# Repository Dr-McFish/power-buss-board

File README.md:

# power-buss-board
power distribution PCB for a cosmo format sythesiser

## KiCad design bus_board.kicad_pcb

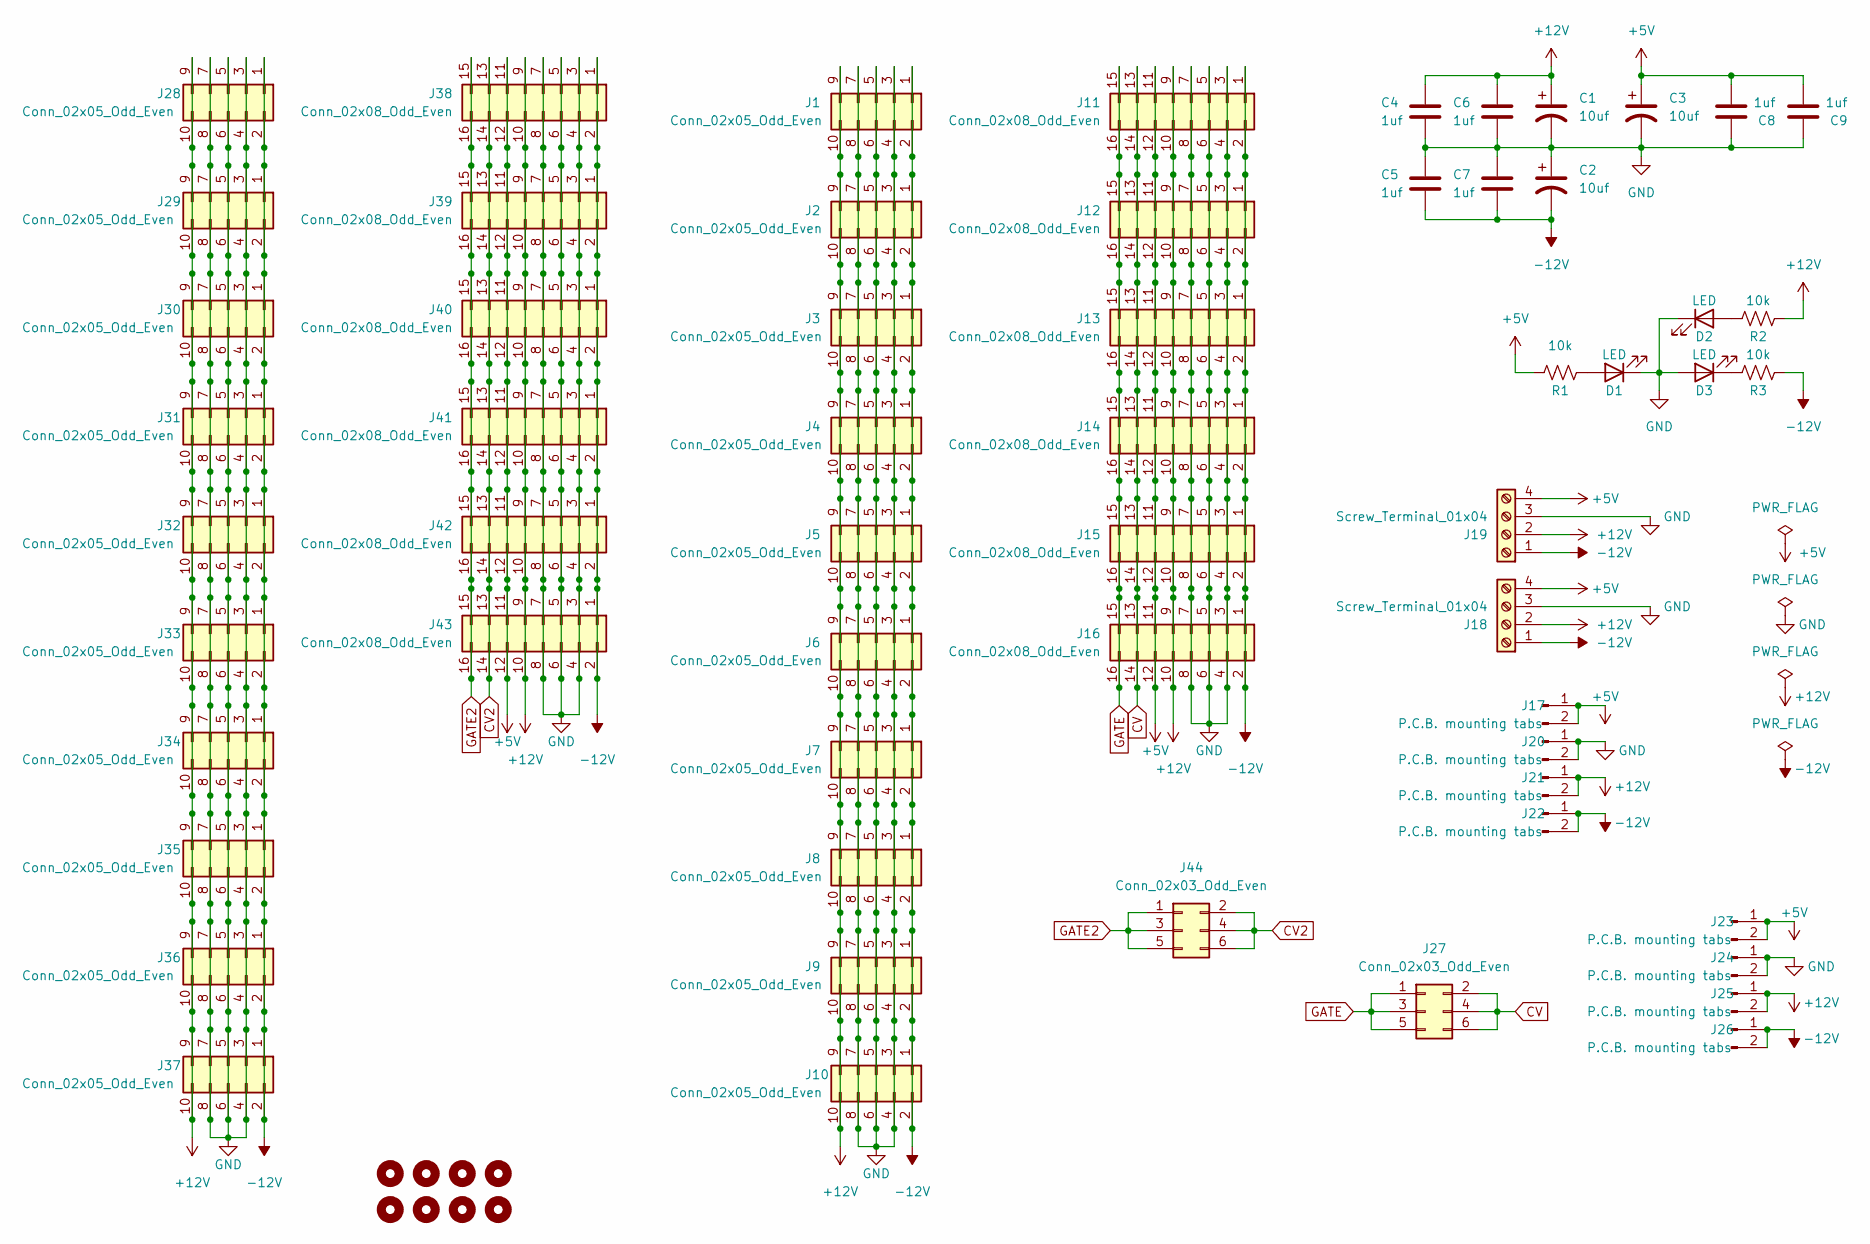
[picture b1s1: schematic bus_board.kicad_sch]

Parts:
C1, C2, C3: 10uf; CP_Radial_D5.0mm_P2.50mm
C4, C5, C6, C7, C8, C9: 1uf; C_Disc_D5.0mm_W2.5mm_P5.00mm
D1, D2, D3: LED; LED_D5.0mm_Clear
H1, H2, H3, H4, H5, H6, H7, H8: MountingHole; MountingHole_3.2mm_M3
J1, J2, J3, J4, J5, J6, J7, J8, J9, J10, J28, J29, J30, J31, J32, J33, J34, J35, J36, J37: Conn_02x05_Odd_Even; IDC-Header_2x05_P2.54mm_Vertical
J11, J12, J13, J14, J15, J16, J38, J39, J40, J41, J42, J43: Conn_02x08_Odd_Even; IDC-Header_2x08_P2.54mm_Vertical
J17, J20, J21, J22, J23, J24, J25, J26: P.C.B. mounting tabs; 3867B.68 P.C.B. mounting tab
J18, J19: Screw_Terminal_01x04; TerminalBlock_bornier-4_P5.08mm
J27, J44: Conn_02x03_Odd_Even; PinHeader_2x03_P2.54mm_Vertical
R1: 10k; R_Axial_DIN0207_L6.3mm_D2.5mm_P10.16mm_Horizontal
R2: 10k; R_Axial_DIN0207_L6.3mm_D2.5mm_P7.62mm_Horizontal
R3: 10k; R_Axial_DIN0207_L6.3mm_D2.5mm_P15.24mm_Horizontal

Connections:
+5V: C3.1, C8.2, C9.2, J11.11, J11.12, J12.11, J12.12, J13.11, J13.12, J14.11, J14.12, J15.11, J15.12, J16.11, J16.12, J17.1, J17.2, J18.4, J19.4, J23.1, J23.2, J38.11, J38.12, J39.11, J39.12, J40.11, J40.12, J41.11, J41.12, J42.11, J42.12, J43.11, J43.12, R1.1
+12V: C1.1, C4.1, C6.1, J1.9, J1.10, J2.9, J2.10, J3.9, J3.10, J4.9, J4.10, J5.9, J5.10, J6.9, J6.10, J7.9, J7.10, J8.9, J8.10, J9.9, J9.10, J10.9, J10.10, J11.9, J11.10, J12.9, J12.10, J13.9, J13.10, J14.9, J14.10, J15.9, J15.10, J16.9, J16.10, J18.2, J19.2, J21.1, J21.2, J25.1, J25.2, J28.9, J28.10, J29.9, J29.10, J30.9, J30.10, J31.9, J31.10, J32.9, J32.10, J33.9, J33.10, J34.9, J34.10, J35.9, J35.10, J36.9, J36.10, J37.9, J37.10, J38.9, J38.10, J39.9, J39.10, J40.9, J40.10, J41.9, J41.10, J42.9, J42.10, J43.9, J43.10, R2.2
-12V: C2.2, C5.2, C7.2, J1.1, J1.2, J2.1, J2.2, J3.1, J3.2, J4.1, J4.2, J5.1, J5.2, J6.1, J6.2, J7.1, J7.2, J8.1, J8.2, J9.1, J9.2, J10.1, J10.2, J11.1, J11.2, J12.1, J12.2, J13.1, J13.2, J14.1, J14.2, J15.1, J15.2, J16.1, J16.2, J18.1, J19.1, J22.1, J22.2, J26.1, J26.2, J28.1, J28.2, J29.1, J29.2, J30.1, J30.2, J31.1, J31.2, J32.1, J32.2, J33.1, J33.2, J34.1, J34.2, J35.1, J35.2, J36.1, J36.2, J37.1, J37.2, J38.1, J38.2, J39.1, J39.2, J40.1, J40.2, J41.1, J41.2, J42.1, J42.2, J43.1, J43.2, R3.2
CV: J11.13, J11.14, J12.13, J12.14, J13.13, J13.14, J14.13, J14.14, J15.13, J15.14, J16.13, J16.14, J27.2, J27.4, J27.6
CV2: J38.13, J38.14, J39.13, J39.14, J40.13, J40.14, J41.13, J41.14, J42.13, J42.14, J43.13, J43.14, J44.2, J44.4, J44.6
GATE: J11.15, J11.16, J12.15, J12.16, J13.15, J13.16, J14.15, J14.16, J15.15, J15.16, J16.15, J16.16, J27.1, J27.3, J27.5
GATE2: J38.15, J38.16, J39.15, J39.16, J40.15, J40.16, J41.15, J41.16, J42.15, J42.16, J43.15, J43.16, J44.1, J44.3, J44.5
GND: C1.2, C2.1, C3.2, C4.2, C5.1, C6.2, C7.1, C8.1, C9.1, D1.1 (K), D2.1 (K), D3.2 (A), J1.3, J1.4, J1.5, J1.6, J1.7, J1.8, J2.3, J2.4, J2.5, J2.6, J2.7, J2.8, J3.3, J3.4, J3.5, J3.6, J3.7, J3.8, J4.3, J4.4, J4.5, J4.6, J4.7, J4.8, J5.3, J5.4, J5.5, J5.6, J5.7, J5.8, J6.3, J6.4, J6.5, J6.6, J6.7, J6.8, J7.3, J7.4, J7.5, J7.6, J7.7, J7.8, J8.3, J8.4, J8.5, J8.6, J8.7, J8.8, J9.3, J9.4, J9.5, J9.6, J9.7, J9.8, J10.3, J10.4, J10.5, J10.6, J10.7, J10.8, J11.3, J11.4, J11.5, J11.6, J11.7, J11.8, J12.3, J12.4, J12.5, J12.6, J12.7, J12.8, J13.3, J13.4, J13.5, J13.6, J13.7, J13.8, J14.3, J14.4, J14.5, J14.6, J14.7, J14.8, J15.3, J15.4, J15.5, J15.6, J15.7, J15.8, J16.3, J16.4, J16.5, J16.6, J16.7, J16.8, J18.3, J19.3, J20.1, J20.2, J24.1, J24.2, J28.3, J28.4, J28.5, J28.6, J28.7, J28.8, J29.3, J29.4, J29.5, J29.6, J29.7, J29.8, J30.3, J30.4, J30.5, J30.6, J30.7, J30.8, J31.3, J31.4, J31.5, J31.6, J31.7, J31.8, J32.3, J32.4, J32.5, J32.6, J32.7, J32.8, J33.3, J33.4, J33.5, J33.6, J33.7, J33.8, J34.3, J34.4, J34.5, J34.6, J34.7, J34.8, J35.3, J35.4, J35.5, J35.6, J35.7, J35.8, J36.3, J36.4, J36.5, J36.6, J36.7, J36.8, J37.3, J37.4, J37.5, J37.6, J37.7, J37.8, J38.3, J38.4, J38.5, J38.6, J38.7, J38.8, J39.3, J39.4, J39.5, J39.6, J39.7, J39.8, J40.3, J40.4, J40.5, J40.6, J40.7, J40.8, J41.3, J41.4, J41.5, J41.6, J41.7, J41.8, J42.3, J42.4, J42.5, J42.6, J42.7, J42.8, J43.3, J43.4, J43.5, J43.6, J43.7, J43.8
unnamed: D1.2 (A), R1.2
unnamed: D2.2 (A), R2.1
unnamed: D3.1 (K), R3.1

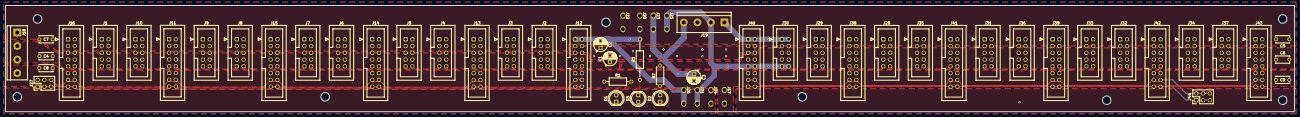
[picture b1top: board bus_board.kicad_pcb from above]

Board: 2 copper layers, 483.9 x 39.9 mm, 67 parts (0 on the bottom side), 11 nets.

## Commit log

2023-05-03 Initialize repository
2023-05-03 add images and schematic
2023-05-03 Implement flood fills for power channels
